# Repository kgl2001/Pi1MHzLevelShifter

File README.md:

# Pi1MHz Level Shifter for use with BBC Micro and Master 128 computers.

This project allows a Raspberry Pi to be connected to the 1MHz port on the BBC Micro and Master 128 computers, and emulates a number of existing Beeb peripherals plus some new ones:

* ADFS Harddisc
* Music 5000 / 3000
* Expansion RAM (480Mbytes for a PiZero)

A PiZero, PiZeroW or PiZero2W and level shifter can sit under a Beeb or Master.

The Pi3A+ and Pi3B+ are also supported via a cable as it won't fit under the computer.

The latest Pi Firmware can be downloaded from the following sites:

https://github.com/dp111/Pi1MHz
https://www.stardot.org.uk/forums/viewtopic.php?t=19513

Some general notes:

* The source files are to be used with KiCAD v9.0.0 or later.
* The gerber files have been optimised for fabrication by JLCPCB. In particular, there is a 8mmx8mm silkscreen box on the rear of the PCB. This is to allow a 2D barcode, with unique serial number to be printed on the PCB.
* If you want the barcode to be added, then make sure to select this option in the 'Mark on PCB' field, and make sure to select 'Specify position' in the '2D Barcode Position' field, otherwise you will end up with a white 8mm x 8mm box printed on your PCB and a 8mm x 8mm barcode printed at a position of JLCPCBs choosing. Thrust me on this!
* If you don't want the barcode added, then remove the 8mm x 8mm box from the silkscreen layer and regenerate the gerbers. Otherwise you will end up with a white 8mm x 8mm box printed on your PCB.
* A combined CPL / BOM file is included in the gerber directory. Again, this is for use with JLCPCB, if you want to use their PCBA (PCB Assembly) to solder on all the SMD parts.
* You will need to source suitable 34 pin right angle and 40 pin straight through sockets, and solder these onto the PCB. The Raspberry Pi will connect to the 40 pin socket and the level shifter will plug into the 1Mhz port via the 34 pin socket.
* Be aware that it is possible to misalign the 34 pin socket both vertically and horizontally when plugging it into the 1MHz port so take care to ensure it is aligned correctly.
* The pins on the 1MHz bus connector may be tarnished if the header has not been used for many years. This can cause unreliable operation. This can usually be fixed with repeated removal and re-insertion of the level shifter into the header.
* Do not use a ribbon cable to connect the Raspberry Pi to the level shifter. Instead, the Raspberry Pi should be plugged directly into the level shifter.
* The level shifter can be plugged directly into the 1MHz bus connector in the well underneath the keyboard, or it can be attached to the 1MHz bus connector via a 34 way male / female ribbon cable.
* There is limited space in the well underneath the Master, so the the level shifter should initially be inserted at an angle and then straightened out as the level shifter is pushed home into the 1MHz bus connector.
* Due to the limited space underneath the Master, a compromise had to be made on the overall size of the level shifter board. Therefore, when fitting the level shifter into the Model B it may not be possible to push the level shifter fully into the 1MHz socket, otherwise the front face of the Pi will clash with part of the computer case. 
* No power is available from the 1MHz bus connector, so a 5v supply to power both the level shifter and Raspberry Pi must be found from elsewhere. A JST-XH (or similar) connector can be added to the level shifter board and both the level shifter board and the Pi can be powered via this connector.
* If attaching the level shifter directly to the 1MHz bus connector, it is possible to pick up a suitable 5v supply from either the tube connector or the user port. A separete supply is not required for the Raspberry Pi in this case. If both these ports are already in use, then an alternative location for powering the level shifter board and Raspberry Pi will need to be found.
* If picking up power from the tube connector or the user port, a small 2 core cable with a JST connector on one end and Dupont connector on the other end is recommended for connecting between the tube connector or the user port and the level shifter.
* If the level shifter is connected to the 1MHz bus connector via a ribbon cable then the simplest way to power the level shifter and Raspberry Pi is via a standard Raspberry Pi power supply connected to the Raspberry Pi. This will also power the level shifter. You should not attempt to use separate power supplies to power both the level shifter and the Raspberry Pi.

Please refer to the following discussion on Stardot for further details: https://www.stardot.org.uk/forums/viewtopic.php?t=18513

## Developer

The 1MHz level shifter board is developed and maintained by Ken Lowe.
    
## Hardware License (Creative Commons BY-SA 4.0)

Please see the following link for details: https://creativecommons.org/licenses/by-sa/4.0/

You are free to:

Share - copy and redistribute the material in any medium or format
Adapt - remix, transform, and build upon the material
for any purpose, even commercially.

This license is acceptable for Free Cultural Works.

The licensor cannot revoke these freedoms as long as you follow the license terms.

Under the following terms:

Attribution - You must give appropriate credit, provide a link to the license, and indicate if changes were made. You may do so in any reasonable manner, but not in any way that suggests the licensor endorses you or your use.

ShareAlike - If you remix, transform, or build upon the material, you must distribute your contributions under the same license as the original.

No additional restrictions - You may not apply legal terms or technological measures that legally restrict others from doing anything the license permits.

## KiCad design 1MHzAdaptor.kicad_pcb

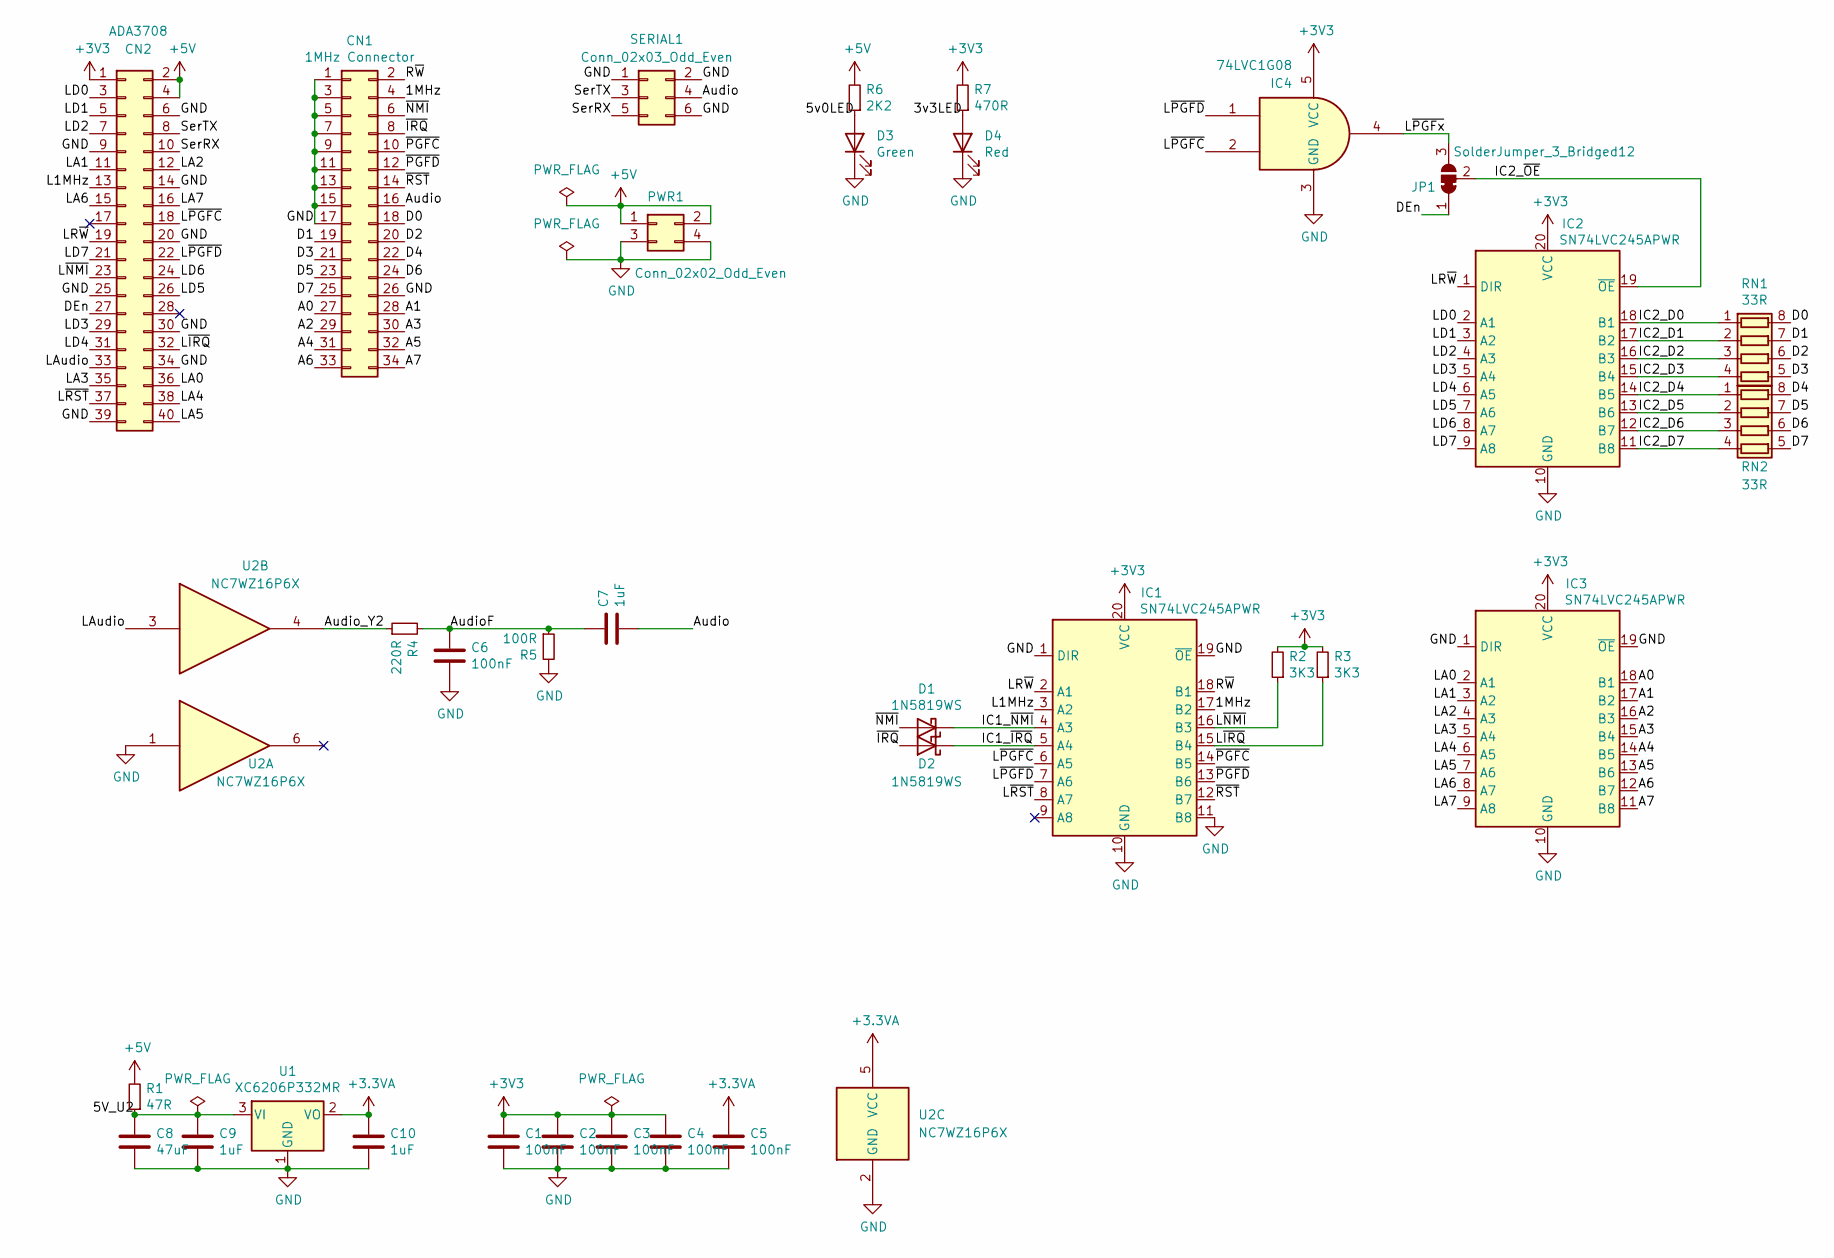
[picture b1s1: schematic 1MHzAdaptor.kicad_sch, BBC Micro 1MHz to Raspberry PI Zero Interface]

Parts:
C1, C3, C4, C5, C6: 100nF; C_0402_1005Metric; JLC Part Number C1525
C2: 100nF; C_0402_1005Metric; LCSC Part # C1525
C7: 1uF; C_1206_3216Metric; JLC Part Number C1848
C8: 47uF; C_0805_2012Metric; JLC Part Number C16780
C9, C10: 1uF; C_0402_1005Metric; JLC Part Number C52923
CN1: 1MHz Connector; PinSocket_2x17_P2.54mm_Horizontal_Reverse
CN2: ADA3708; PinSocket_2x20_P2.54mm_Vertical
D1, D2: 1N5819WS; D_SOD-323; JLC Part Number C191023
D3: Green; LED_0603_1608Metric; JLC Part Number C72043
D4: Red; LED_0603_1608Metric; JLC Part Number C2286
IC1, IC2, IC3: SN74LVC245APWR; TSSOP-20_4.4x6.5mm_P0.65mm; JLC Part Number C7848
IC4: 74LVC1G08; SOT-23-5
JP1: SolderJumper_3_Bridged12; SolderJumper-3_P1.3mm_Bridged12_RoundedPad1.0x1.5mm_NumberL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
PWR1: Conn_02x02_Odd_Even; PinHeader_2x02_P2.54mm_Horizontal
R1: 47R; R_0402_1005Metric; JLC Part Number C25118
R2, R3: 3K3; R_0402_1005Metric; JLC Part Number C25890
R4: 220R; R_0402_1005Metric; JLC Part Number C25091
R5: 100R; R_0402_1005Metric; JLC Part Number C25076
R6: 2K2; R_0402_1005Metric; JLC Part Number C25879
R7: 470R; R_0402_1005Metric; JLC Part Number C25117
RN1, RN2: 33R; R_Array_Concave_4x0402; JLC Part Number C25501
SERIAL1: Conn_02x03_Odd_Even; PinHeader_2x03_P2.54mm_Horizontal
U1: XC6206P332MR; SOT-23-3; JLC Part Number C5446
U2: NC7WZ16P6X; SOT-363_SC-70-6; JLC Part Number C114148

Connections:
+3.3VA: C5.1, C10.1, U1.2 (VO), U2.5 (VCC)
+3V3: C1.1, C2.1, C3.1, C4.1, CN2.1, IC1.20 (VCC), IC2.20 (VCC), IC3.20 (VCC), IC4.5 (VCC), R2.2, R3.2, R7.2
+5V: CN2.2, CN2.4, PWR1.1, PWR1.2, R1.2, R6.2
/1MHz: CN1.4, IC1.17 (B2)
/3v3LED: D4.2 (A), R7.1
/5V_U2: C8.1, C9.1, R1.1, U1.3 (VI)
/5v0LED: D3.2 (A), R6.1
/A0: CN1.27, IC3.18 (B1)
/A1: CN1.28, IC3.17 (B2)
/A2: CN1.29, IC3.16 (B3)
/A3: CN1.30, IC3.15 (B4)
/A4: CN1.31, IC3.14 (B5)
/A5: CN1.32, IC3.13 (B6)
/A6: CN1.33, IC3.12 (B7)
/A7: CN1.34, IC3.11 (B8)
/Audio: C7.2, CN1.16, SERIAL1.4
/AudioF: C6.1, C7.1, R4.2, R5.1
/Audio_Y2: R4.1, U2.4
/D0: CN1.18, RN1.8 (R1.2)
/D1: CN1.19, RN1.7 (R2.2)
/D2: CN1.20, RN1.6 (R3.2)
/D3: CN1.21, RN1.5 (R4.2)
/D4: CN1.22, RN2.8 (R1.2)
/D5: CN1.23, RN2.7 (R2.2)
/D6: CN1.24, RN2.6 (R3.2)
/D7: CN1.25, RN2.5 (R4.2)
/DEn: CN2.27, JP1.1 (A)
/IC1_~IRQ: D2.1 (K), IC1.5 (A4)
/IC1_~NMI: D1.1 (K), IC1.4 (A3)
/IC2_D0: IC2.18 (B1), RN1.1 (R1.1)
/IC2_D1: IC2.17 (B2), RN1.2 (R2.1)
/IC2_D2: IC2.16 (B3), RN1.3 (R3.1)
/IC2_D3: IC2.15 (B4), RN1.4 (R4.1)
/IC2_D4: IC2.14 (B5), RN2.1 (R1.1)
/IC2_D5: IC2.13 (B6), RN2.2 (R2.1)
/IC2_D6: IC2.12 (B7), RN2.3 (R3.1)
/IC2_D7: IC2.11 (B8), RN2.4 (R4.1)
/IC2_~OE: IC2.19 (~OE), JP1.2 (C)
/L1MHz: CN2.13, IC1.3 (A2)
/LA0: CN2.36, IC3.2 (A1)
/LA1: CN2.11, IC3.3 (A2)
/LA2: CN2.12, IC3.4 (A3)
/LA3: CN2.35, IC3.5 (A4)
/LA4: CN2.38, IC3.6 (A5)
/LA5: CN2.40, IC3.7 (A6)
/LA6: CN2.15, IC3.8 (A7)
/LA7: CN2.16, IC3.9 (A8)
/LAudio: CN2.33, U2.3
/LD0: CN2.3, IC2.2 (A1)
/LD1: CN2.5, IC2.3 (A2)
/LD2: CN2.7, IC2.4 (A3)
/LD3: CN2.29, IC2.5 (A4)
/LD4: CN2.31, IC2.6 (A5)
/LD5: CN2.26, IC2.7 (A6)
/LD6: CN2.24, IC2.8 (A7)
/LD7: CN2.21, IC2.9 (A8)
/LR~W: CN2.19, IC1.2 (A1), IC2.1 (DIR)
/L~IRQ: CN2.32, IC1.15 (B4), R3.1
/L~NMI: CN2.23, IC1.16 (B3), R2.1
/L~PGFC: CN2.18, IC1.6 (A5), IC4.2
/L~PGFD: CN2.22, IC1.7 (A6), IC4.1
/L~PGFx: IC4.4, JP1.3 (B)
/L~RST: CN2.37, IC1.8 (A7)
/R~W: CN1.2, IC1.18 (B1)
/SerRX: CN2.10, SERIAL1.5
/SerTX: CN2.8, SERIAL1.3
/~IRQ: CN1.8, D2.2 (A)
/~NMI: CN1.6, D1.2 (A)
/~PGFC: CN1.10, IC1.14 (B5)
/~PGFD: CN1.12, IC1.13 (B6)
/~RST: CN1.14, IC1.12 (B7)
GND: C1.2, C2.2, C3.2, C4.2, C5.2, C6.2, C8.2, C9.2, C10.2, CN1.1, CN1.3, CN1.5, CN1.7, CN1.9, CN1.11, CN1.13, CN1.15, CN1.17, CN1.26, CN2.6, CN2.9, CN2.14, CN2.20, CN2.25, CN2.30, CN2.34, CN2.39, D3.1 (K), D4.1 (K), IC1.1 (DIR), IC1.10 (GND), IC1.11 (B8), IC1.19 (~OE), IC2.10 (GND), IC3.1 (DIR), IC3.10 (GND), IC3.19 (~OE), IC4.3 (GND), PWR1.3, PWR1.4, R5.2, SERIAL1.1, SERIAL1.2, SERIAL1.6, U1.1 (GND), U2.1, U2.2 (GND)

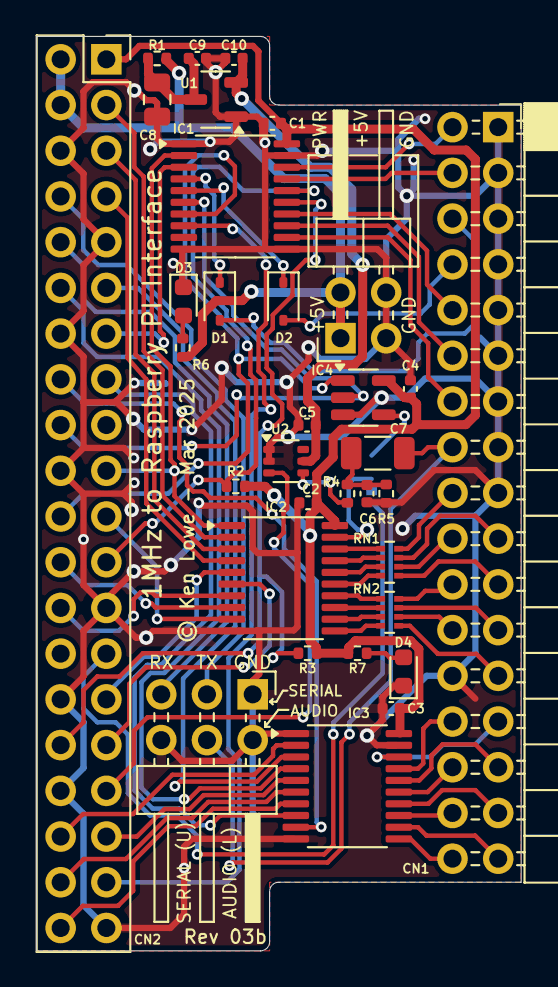
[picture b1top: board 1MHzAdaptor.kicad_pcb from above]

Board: 2 copper layers, 26.9 x 50.8 mm, 34 parts (1 on the bottom side), 72 nets.

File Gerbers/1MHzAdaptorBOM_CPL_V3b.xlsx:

Designator | LCSC Part # | Footprint | JLCValue | Mid X | Mid Y | Rot | Side | Val | Package
C1 | C1525 | 0402 | 100nF | 137.18539999999999 | -59.436 | 180 | top | 100nF | C_0402_1005Metric
C2 | C1525 | 0402 | 100nF | 139.19200000000001 | -80.518000000000001 | 180 | top | 100nF | C_0402_1005Metric
C3 | C1525 | 0402 | 100nF | 143.81479999999999 | -91.947999999999993 | 180 | top | 100nF | C_0402_1005Metric
C4 | C1525 | 0402 | 100nF | 144.88159999999999 | -74.193399999999997 | 90 | top | 100nF | C_0402_1005Metric
C5 | C1525 | 0402 | 100nF | 139.1412 | -76.2 | 180 | top | 100nF | C_0402_1005Metric
C6 | C1525 | 0402 | 100nF | 142.46860000000001 | -80.010000000000005 | 270 | top | 100nF | C_0402_1005Metric
C7 | C1848 | 1206 | 1uF | 143.06549999999999 | -77.762100000000004 | 0 | top | 1uF | C_1206_3216Metric
C8 | C16780 | 0805 | 47uF | 130.81 | -58.115200000000002 | 270 | top | 47uF | C_0805_2012Metric
C9 | C52923 | 0402 | 1uF | 133.04519999999999 | -55.8292 | 0 | top | 1uF | C_0402_1005Metric
C10 | C52923 | 0402 | 1uF | 135.0772 | -55.8292 | 180 | top | 1uF | C_0402_1005Metric
D1 | C191023 | SOD-323 | 1N5819WS | 134.2884 | -69.329300000000003 | 270 | top | 1N5819WS | D_SOD-323
D2 | C191023 | SOD-323 | 1N5819WS | 137.82040000000001 | -69.329300000000003 | 270 | top | 1N5819WS | D_SOD-323
D3 | C72043 | 0603 | Green | 132.2705 | -69.329300000000003 | 270 | top | LED | LED_0603_1608Metric
D4 | C2286 | 0603 | Red | 144.50059999999999 | -89.890600000000006 | 90 | top | LED | LED_0603_1608Metric
IC1 | C460537 | TSSOP-20 | SN74LVC245APWR | 135.1534 | -63.5 | 270 | top | SN74LVC245APWR | TSSOP-20_4.4x6.5mm_P0.65mm
IC2 | C460537 | TSSOP-20 | SN74LVC245APWR | 137.82040000000001 | -84.709000000000003 | -90 | top | SN74LVC245APWR | TSSOP-20_4.4x6.5mm_P0.65mm
IC3 | C460537 | TSSOP-20 | SN74LVC245APWR | 141.37639999999999 | -96.266000000000005 | 270 | top | SN74LVC245APWR | TSSOP-20_4.4x6.5mm_P0.65mm
IC4 | C434068 | SOT-23-5 | 74LVC1G08 | 142.2654 | -74.676000000000002 | 180 | top | 74LVC1G08 | SOT-23-5
R1 | C25118 | 0402 | 47R | 130.81 | -55.8292 | 0 | top | 47R | R_0402_1005Metric
R2 | C25890 | 0402 | 3K3 | 135.1788 | -79.6036 | 0 | top | 3K3 | R_0402_1005Metric
R3 | C25890 | 0402 | 3K3 | 139.16659999999999 | -88.874600000000001 | 0 | top | 3K3 | R_0402_1005Metric
R4 | C25091 | 0402 | 220R | 141.37639999999999 | -80.010000000000005 | 90 | top | 220R | R_0402_1005Metric
R5 | C25076 | 0402 | 100R | 143.53540000000001 | -80.010000000000005 | 270 | top | 100R | R_0402_1005Metric
R6 | C25879 | 0402 | 2K2 | 132.23240000000001 | -71.905000000000001 | 270 | top | 2K2 | R_0402_1005Metric
R7 | C25117 | 0402 | 470R | 141.9376 | -88.874600000000001 | 180 | top | 470R | R_0402_1005Metric
RN1 | C25501 | 0402_x4 | 33R | 143.7259 | -83.82 | 270 | top | 33R | R_Array_Concave_4x0402
RN2 | C25501 | 0402_x4 | 33R | 143.7259 | -86.602000000000004 | 270 | top | 33R | R_Array_Concave_4x0402
U1 | C5446 | SOT-23-3 | XC6206P332MR | 134.06120000000001 | -58.115200000000002 | 0 | top | XC6206P332MR | SOT-23
U2 | C114148 | SOT-363 | NC7WZ16P6X | 137.97280000000001 | -78.206599999999995 | 180 | top | NC7WZ16P6X | SOT-363_SC-70-6

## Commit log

2025-03-30 First public release

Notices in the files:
1MHzAdaptor.kicad_pcb:
© Ken Lowe - Mar 2025
